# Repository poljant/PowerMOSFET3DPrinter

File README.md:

# PowerMOSFET3DPrinter

Układ zasilający grzałki extrudera i stołu drukarki 3D.
Wprawdzie takie układy są dostepne w Internecie, ale ja mam wszystkie części, dlatego postanowiłem zrobić własny układ.
Mój układ zasila obie grzałki.
Część z mniejszym radiatorem do grzałki extrudera, a z większym do grzałki stołu.
Wymiary płytki mogłyby być mniejsze, ale wykonany układ daje możliwość założenia większych radiatorów.
Zasilanie układu tylko 12V, bo nie planowałem zasilania 24V.
Aby korzystać z zasilania 24V (lub innego) dla stołu, można dołożyć kolejną łączówkę.
Wtedy trzeba przeciąć sieżkę +12V i podłączyć +24V, a -24V połaczyć z masą -12V.
Płytka zaprojektowana jest programem KiCad.
Można wprowadzić własne zmiany.

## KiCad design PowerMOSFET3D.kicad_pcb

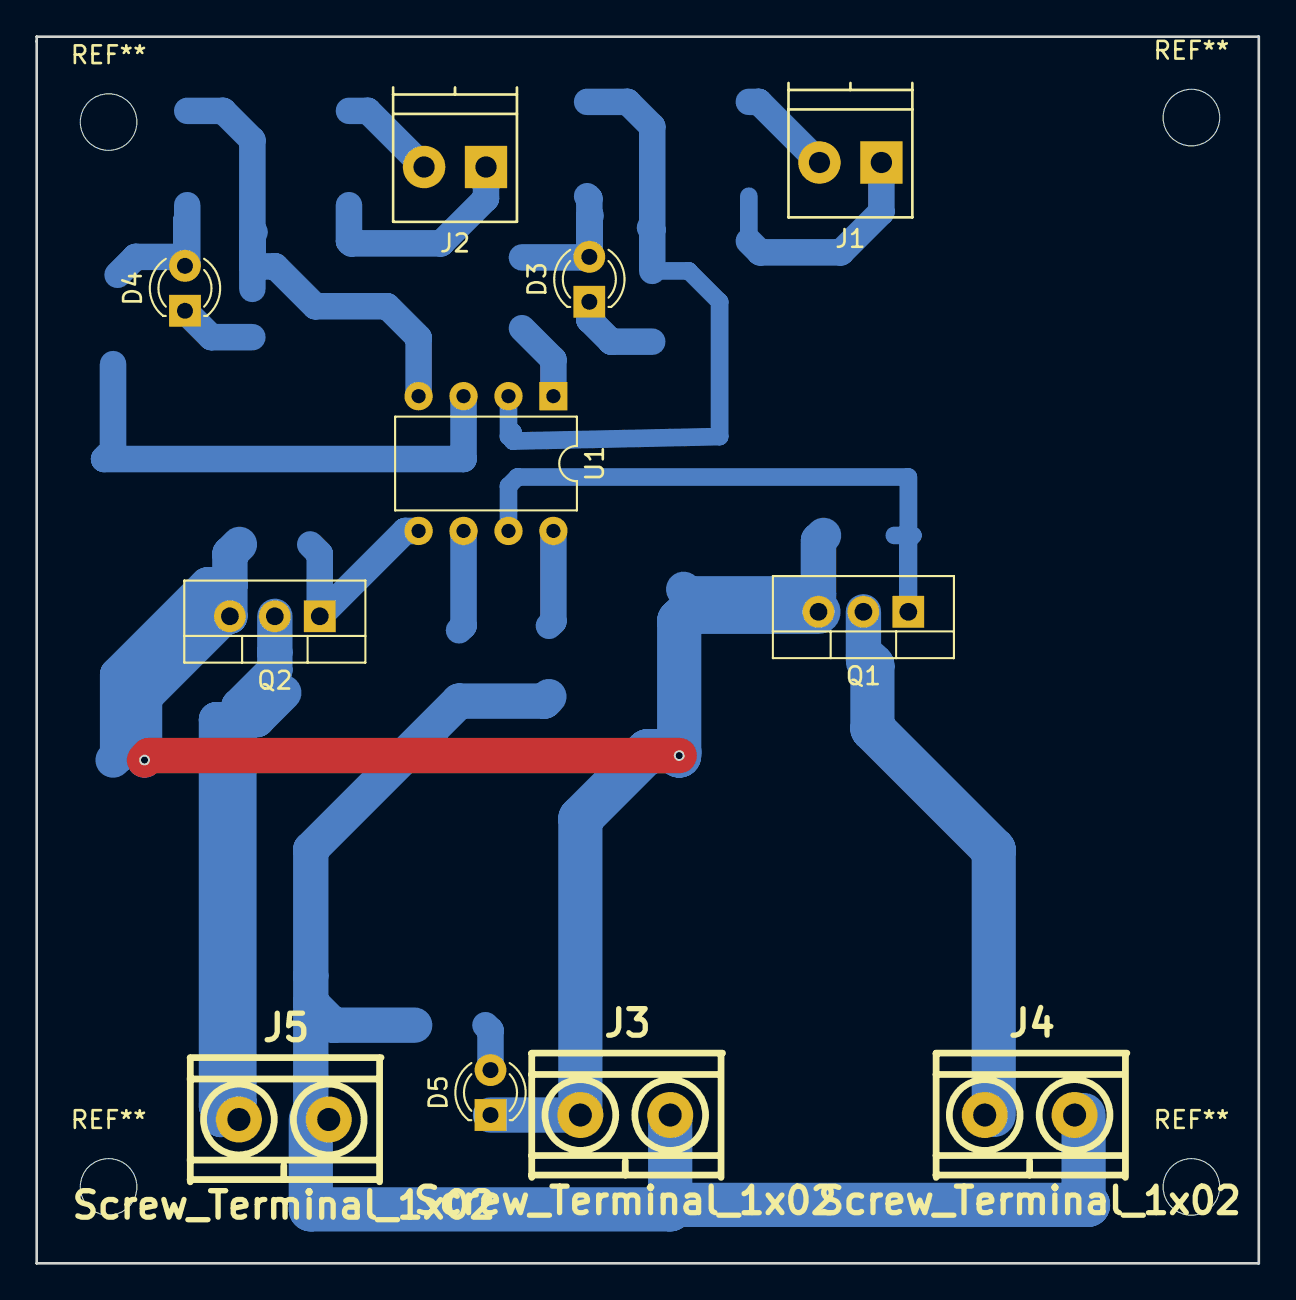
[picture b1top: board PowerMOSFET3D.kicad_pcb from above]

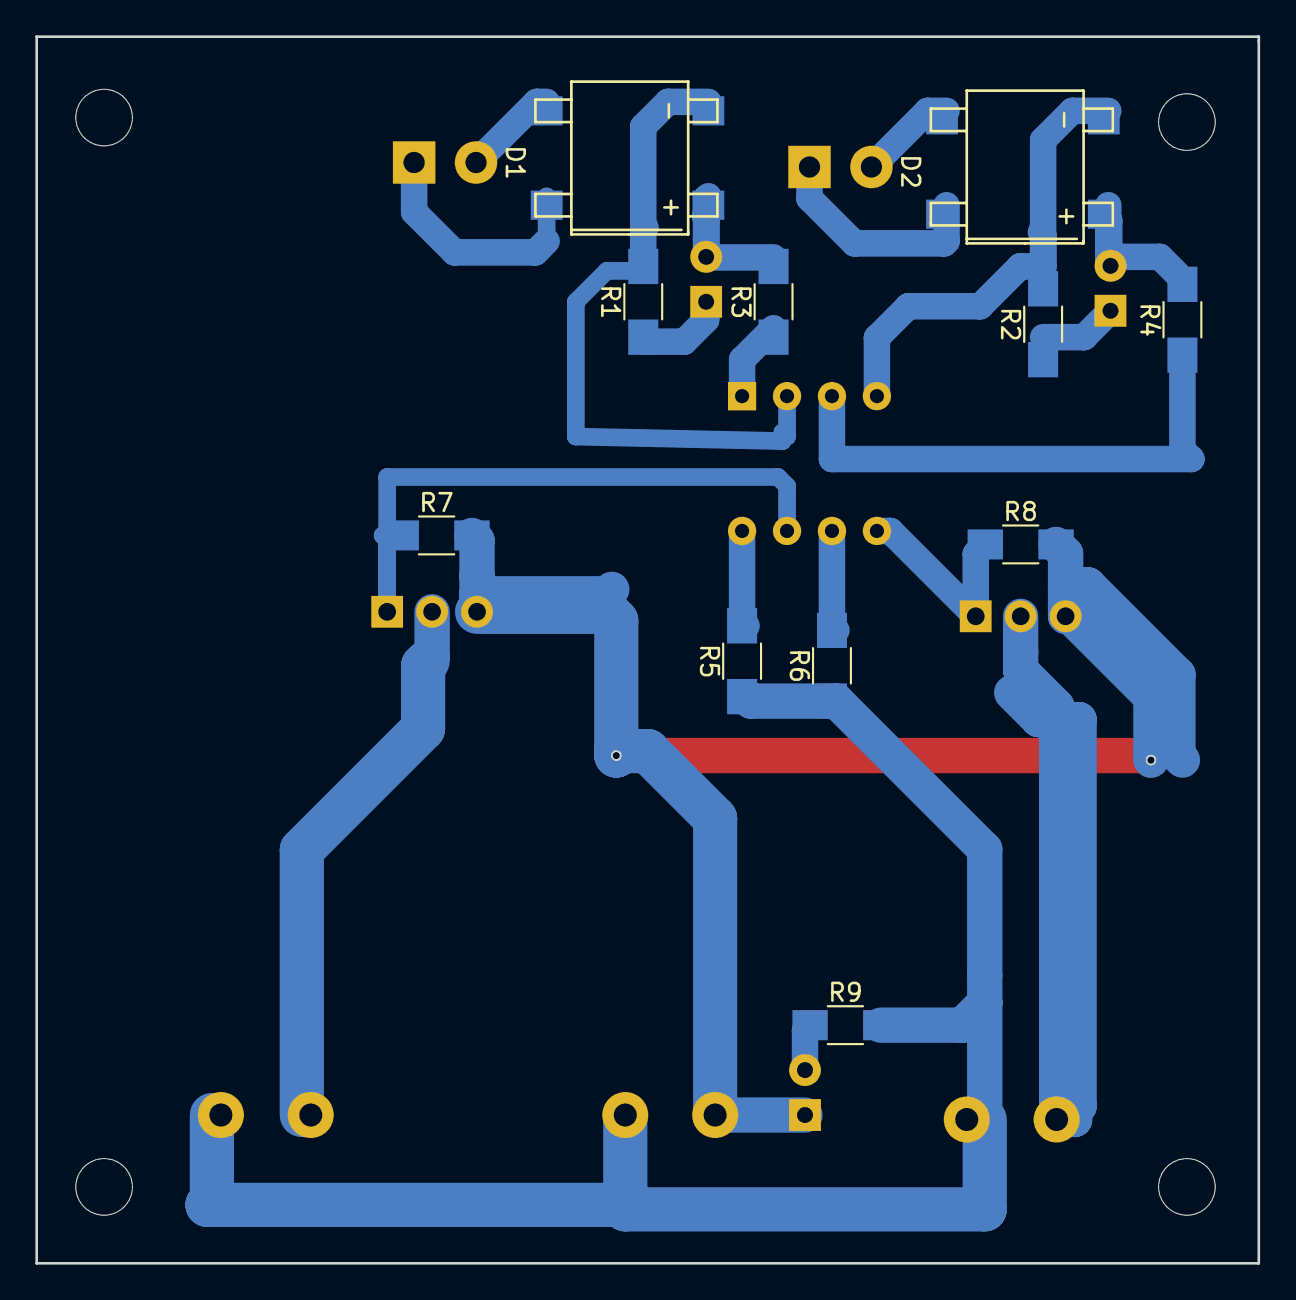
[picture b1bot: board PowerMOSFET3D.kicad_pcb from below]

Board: 2 copper layers, 69.1 x 69.3 mm, 22 parts (11 on the bottom side), 21 nets.

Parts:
D1, D2: DF08S; DF08S_Bridge_Gretza_DFS
D3, D4, D5: LED; LED_D3.0mm
J1, J2: Screw_Terminal_1x02; TerminalBlock_Pheonix_PT-3.5mm_2pol
J3, J4, J5: Screw_Terminal_1x02; gmkds_3-2-5
Q1, Q2: IRLB8721PBF; TO-220_Vertical
R1, R2, R9: 10k; R_1206_HandSoldering
R3, R4: 4k7; R_1206_HandSoldering
R5, R6, R7, R8: R; R_1206_HandSoldering
U1: PC827; DIP-8_W7.62mm

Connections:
GND: D5.1, J3.1, Q1.3, Q2.3, R7.2, R8.2
unnamed: D1.1, D3.2, R3.2
unnamed: D1.2, R1.2, U1.2
unnamed: D1.3, J1.1
unnamed: D1.4, J1.2
unnamed: D2.1, D4.2, R4.2
unnamed: D2.2, R2.2, U1.4
unnamed: D2.3, J2.1
unnamed: D2.4, J2.2
unnamed: D3.1, R1.1
unnamed: D4.1, R2.1
unnamed: D5.2, R9.1
unnamed: J4.1, Q1.2
unnamed: J5.1, Q2.2
unnamed: Q1.1, R7.1, U1.7
unnamed: Q2.1, R8.1, U1.5
unnamed: R3.1, U1.1
unnamed: R4.1, U1.3
unnamed: R5.2, U1.8
unnamed: R6.2, U1.6
VCC: J3.2, J4.2, J5.2, R5.1, R6.1, R9.2

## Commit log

2018-02-28 inicjalizacja projektu
2018-02-28 usunięto wymiar na PCB.
